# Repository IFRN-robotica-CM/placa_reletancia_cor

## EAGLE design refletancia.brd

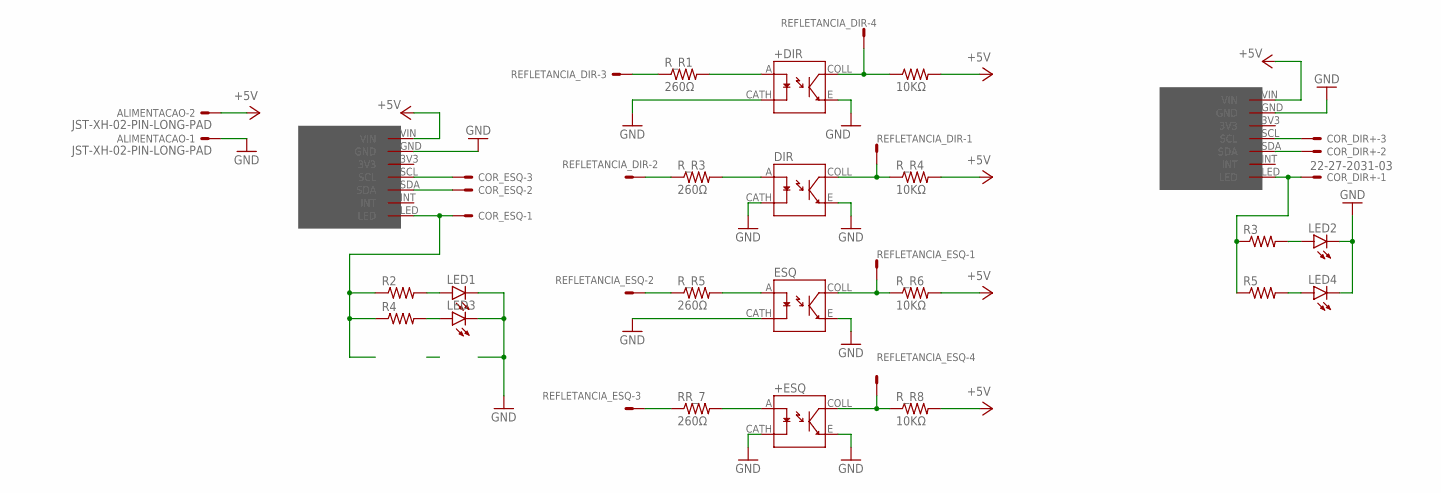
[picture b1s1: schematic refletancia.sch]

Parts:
+DIR: TCRT5000; OPTO_TCRT5000
+ESQ: TCRT5000; OPTO_TCRT5000
ALIMENTACAO: JST-XH-02-PIN-LONG-PAD; JST-XH-02-PACKAGE-LONG-PAD
COR_DIR+: 22-27-2031-03; 6410-03
COR_ESQ: 22-27-2031-03; 6410-03
DIR: TCRT5000; OPTO_TCRT5000
ESQ: TCRT5000; OPTO_TCRT5000
LED1, LED2: LED5MM
LED3, LED4: LEDCHIP-LED0805; CHIP-LED0805
R2, R3, R4, R5: R-US_0204/7; 0204/7
REFLETANCIA_DIR: JST-XH-04-PIN-LONG-PAD; JST-XH-04-PACKAGE-LONG-PAD
REFLETANCIA_ESQ: JST-XH-04-PIN-LONG-PAD; JST-XH-04-PACKAGE-LONG-PAD
RR_7: 260Ω; 0204/7
R_R1, R_R5: 260Ω; 0204/7
R_R2, R_R4, R_R8: 10KΩ; 0204/7
R_R3: 260Ω; 0414/15_LOG_PAD
R_R6: 10KΩ; 0207/7_LONG_PAD2
U$1, U$2: TCS34725SEM_FUROS; TCS34725_SEM_FUROS

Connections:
+5V: ALIMENTACAO.2, R_R2.2, R_R4.2, R_R6.2, R_R8.2, U$1.VIN, U$2.VIN
ANALOG_+DIR.: +DIR.COLL, REFLETANCIA_DIR.4, R_R2.1
ANALOG_+ESQ: +ESQ.COLL, REFLETANCIA_ESQ.4, R_R8.1
ANALOG_DIR: DIR.COLL, REFLETANCIA_DIR.1, R_R4.1
ANALOG_ESQ: ESQ.COLL, REFLETANCIA_ESQ.1, R_R6.1
DIGITAL_+DIR.: REFLETANCIA_DIR.3, R_R1.1
DIGITAL_+ESQ: REFLETANCIA_ESQ.3, RR_7.1
DIGITAL_DIR: REFLETANCIA_DIR.2, R_R3.1
DIGITAL_ESQ: REFLETANCIA_ESQ.2, R_R5.1
GND: +DIR.CATH, +DIR.E, +ESQ.CATH, +ESQ.E, ALIMENTACAO.1, DIR.CATH, DIR.E, ESQ.CATH, ESQ.E, LED1.K (C), LED2.K (C), LED3.C, LED4.C, U$1.GND, U$2.GND
unnamed: +DIR.A, R_R1.2
unnamed: DIR.A, R_R3.2
unnamed: ESQ.A, R_R5.2
unnamed: +ESQ.A, RR_7.2
unnamed: COR_ESQ.1, R2.1, R4.1, U$1.LED
unnamed: COR_ESQ.2, U$1.SDA
unnamed: COR_ESQ.3, U$1.SCL
unnamed: COR_DIR+.3, U$2.SCL
unnamed: COR_DIR+.2, U$2.SDA
unnamed: LED1.A, R2.2
unnamed: LED3.A, R4.2
unnamed: LED2.A, R3.2
unnamed: LED4.A, R5.2
unnamed: COR_DIR+.1, R3.1, R5.1, U$2.LED

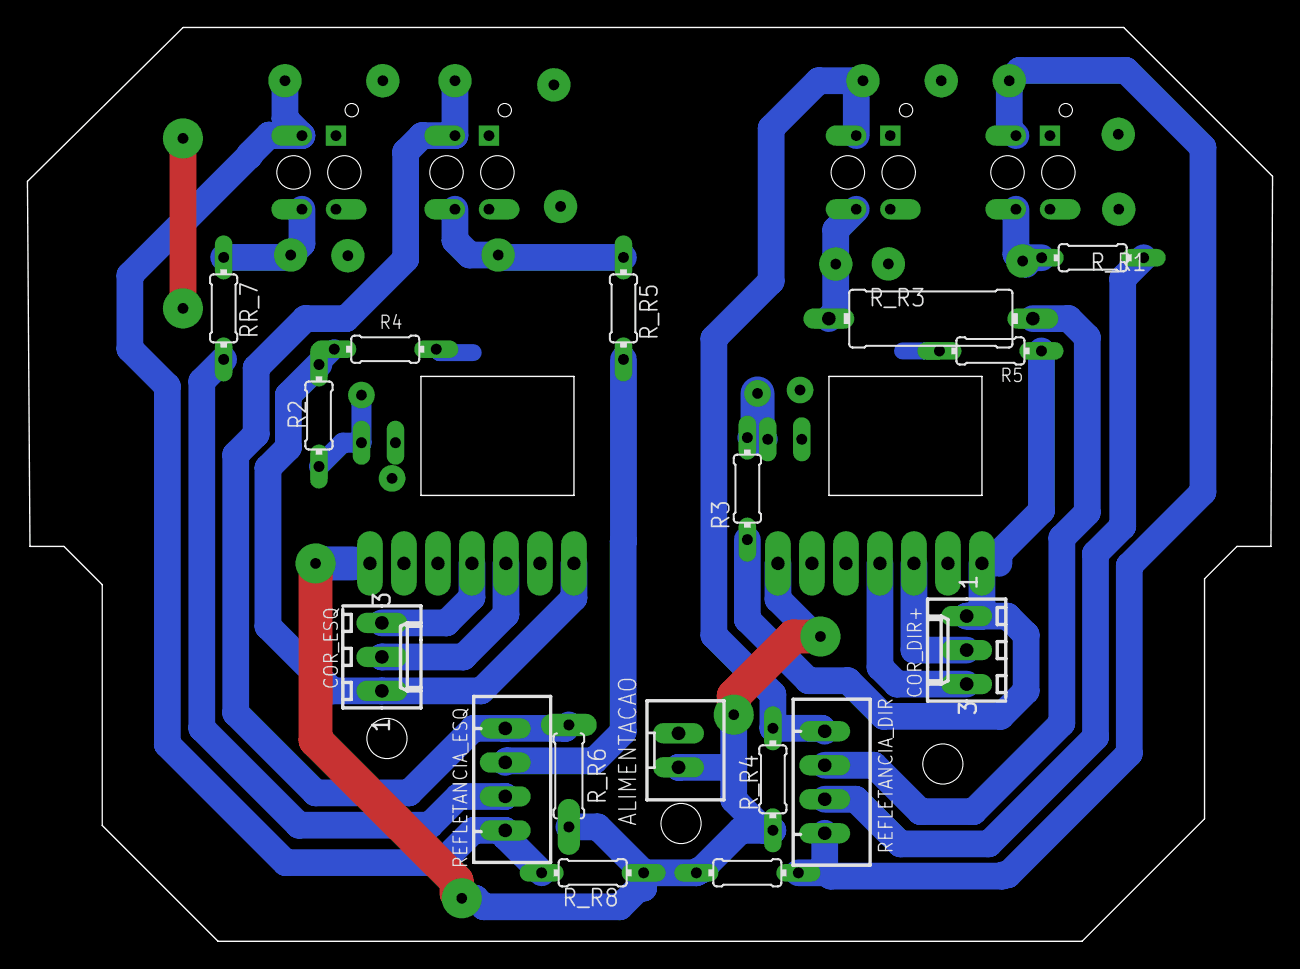
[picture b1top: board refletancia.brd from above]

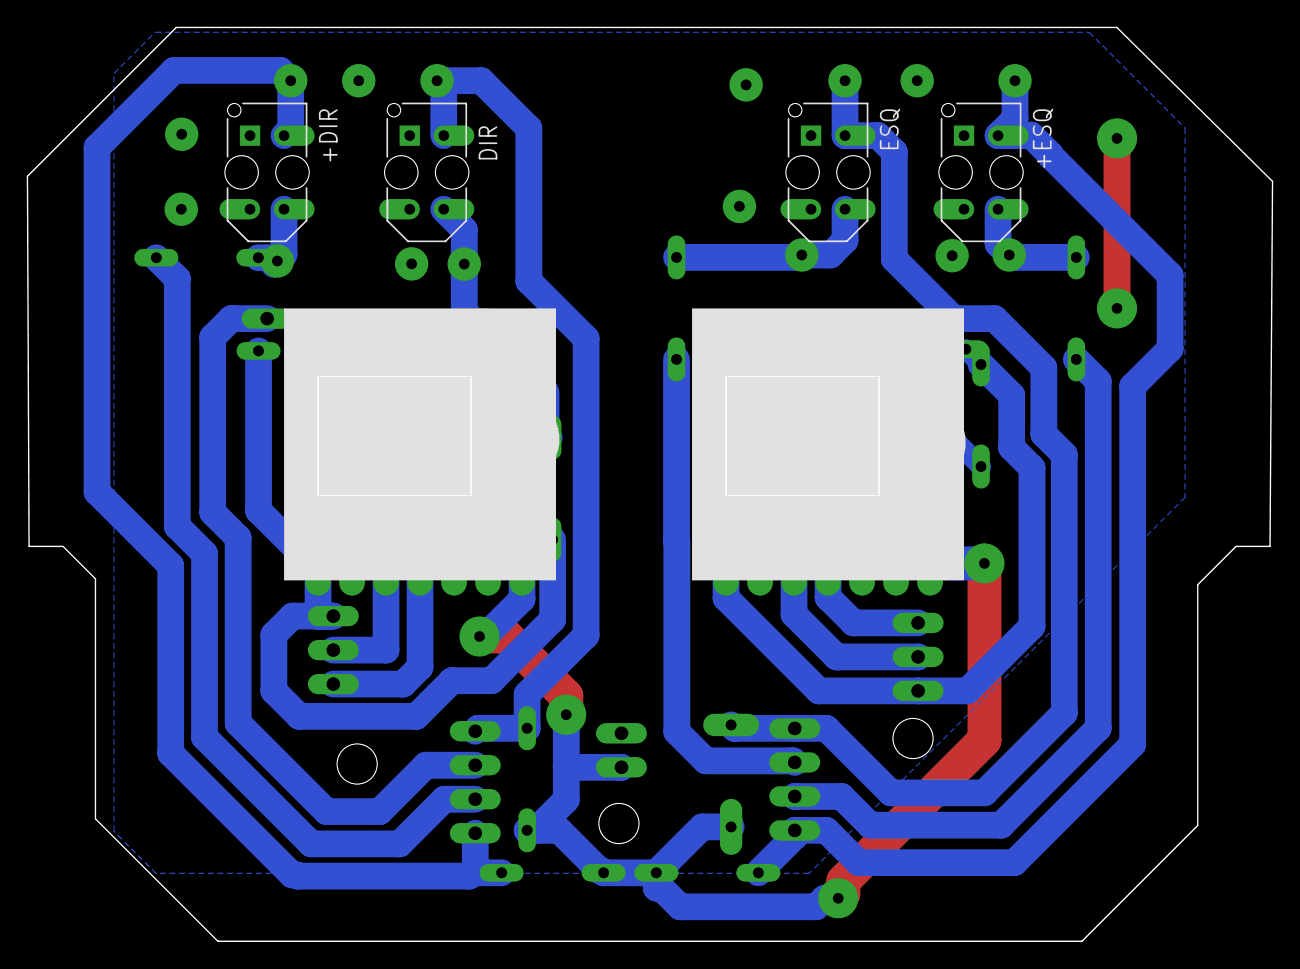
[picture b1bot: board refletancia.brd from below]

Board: 2 copper layers, 93.0 x 68.3 mm, 27 parts (10 on the bottom side), 24 nets.

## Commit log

2023-12-01 adição de arquivos no commit inicial
2024-02-29 Alteração da dimensão e posição de furos
    Os furos de fixação foram alterados, a posição dos conectores do sensor de cor também foi alterada, a dimensão da placa também foi alterada assim como posição de várias trilhas foi trocada
2024-02-29 Adição do arquivo gitignore
